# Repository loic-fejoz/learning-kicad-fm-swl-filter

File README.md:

---
title: De rien à un filtre FM pour SWL
author: Loïc Féjoz
date: September, 2022
fontfamily: times
---
De rien à un filtre FM pour SWL
===============================

# Objectifs

> "Dans un voyage ce n'est pas la destination qui compte mais toujours le chemin parcouru, et les détours surtout."  
> — <cite>Philippe Pollet-Villard</cite>

Vous avez acheté une clef SDR ? Moi aussi. Vous avez commencé à faire un peu d'écoute. Peut-être avez-vous fabriqué votre propre antenne aussi ? Viens alors l'idée de passer à la vitesse supérieure et fabriquer vos propres circuits comme un transceiver par exemple, ou un LNA ou...

Mais ces circuits sont déjà d'un niveau supérieur. J'ai donc voulu expérimenter la création d'une carte plus simple depuis sa conception, son analyse, jusqu'à son expérimentation. Or les ondes de station FM se superposent souvent au signal que l'on veut écouter diminuant par la même la dynamique que l'on perçoit. Dés lors le voyage dans la création d'un **filtre passe-haut** peut commencer ...avec ses détours!

NB&nbsp;: vous l'aurez compris, je suis un [n00b](https://fr.wikipedia.org/wiki/Newbie).

Autres projets similaires dans l'esprit :

* [Filtre coupe-bande FM 88 à 108MHz, de la conception à la réalisation](https://www.f4iha.fr/2021/10/16/filtre-coupe-bande-fm-88-a-108mhz-de-la-conception-a-la-realisation/)

# Conception

Bien évidemment un filtre coupe-bande FM serait probablement plus approprié, surtout s'il est bien net. Mais je voulais quelque chose d'encore plus simple. Retrouvons nous donc sur https://rf-tools.com/lc-filter/ pour concevoir ce filtre de Chebyshev d'ordre 5 avec pour fréquence de coupure 120MHz. Les impédances d'entrée et de sortie seront bien entendus de 50Ω comme l'antene et la clef SDR. 

Au final, ce sera donc 3 condensateurs, 2 inductances, et bien sûr 2 connecteurs SMA. Au passage, rf-tools.com peut aussi fournir des valeurs standardisées mais nous n'allons pas utiliser cette fonctionalité qui sera l'occasion d'un détour.

# Schématique KiCad

Il est donc temps maintenant de passer sous KiCad pour éditer la schématique du projet. Cette étape est relativement aisée et il n'y a pas besoin de faire appel à des librairies externes.

Au passage, le connecteur SMA est un connecteur coaxial générique et "SMA" n'est que le label :

Comme on peut le voir dans la boite de dialogue ci-dessus, on peut définir un modèle spice. Or Spice, c'est pour de la simulation. Directement dans KiCad, il est en effet possible d'[inspecter par simulation le circuit](https://www.kicad.org/discover/spice/). Dans notre cas, il faut donc remplacer J2 par une simple résistance :

J1 devrait être remplacée par une source alternative en série avec une résistance de 50Ω. Mais là, rien de vraiment simple dans cette boite de dialogue. Enfin si, on pourrait utiliser un modèle externe. C'est-à-dire créé un fichier `.lib` qui décrirait cette source alternative et la résistance en série. Mais il apparait alors plus simple de rajouter dans le schéma les élements de simulation :

Il y a même une catégorie de composants "pspice". Par contre, il faut tout de même indiquer qu'ils ne font pas partie véritablement de la liste du matériel ainsi que du circuit imprimé.

Enfin, concernant la source de tension, il faudra la configurer en source alternative d'amplitude 1. La fréquence n'aura pas de conséquence vu les analyses que l'on fera.

# Simulation Spice dans KiCad

Il est temps de lancer la simulation via le menu `Inspecter > Simulateur...` ce qui ouvrira la fenêtre dédiée. Le bouton `Paramètres Sim` ouvrira la boîte de dialogue suivante :

Une fois l'analyse désirée indiqué, à savoir analyser la réponse en fréquence sur la place 80MHz-180MHz par exemple, puis avoir lancer la simulation, on peut alors utiliser le bouton `Sonde` pour aller choisir *sur le schéma* le point de sortie du filtre. On voit alors apparaître la réponse de notre filtre :

On retrouve bien la courbe caractéristique d'un filtre passe-haut. Mais nous avions laissé de côté la valeur des composants à réellement utiliser et si vous avez bien observé, les valeurs sont même différentes dans mes différentes captures d'écran. Il est donc temps de comprendre l'impact de ces valeurs. On peut tester l'impact en restant dans KiCad avec le bouton `Ajustage` puis en sélectionnant un composant. Mais J'aimerais une visualisation plus systématique...

# Simulation LTSpice

Il existe plusieurs simulateurs Spice et KiCad permet facilement d'exporter notre schéma dans ce format via le menu `Exporter > Netliste... > Spice`.

[LTSpice](https://www.analog.com/en/design-center/design-tools-and-calculators/ltspice-simulator.html) est un de ces simulateurs qui peut donc analyser ce circuit. Il suffit de rajouter la ligne suivante dans le fichier (avant le `.end`) pour lancer la même analyse:

```spice
.ac LIN 100 88Meg 180Meg
```

Bien évidement, nous retrouvons alors le même résultat que directement dans KiCad. Mais Spice permet bien plus. Nous pouvons notamment définir des variables globales et demander au simulateur de lancer plusieurs simulations. Par exemple, on peut évaluer une liste précise de valeurs comme suit :

```spice
...
L1 Net-_C1-Pad2_ GND {L}
...
.step param L LIST 40nH 41nH 0.0426uH 45nH 48nH
```

Ou bien encore définir une borne haute, et basse, ainsi que l'incrément

```
...
C2 Net-_C1-Pad2_ Net-_C2-Pad2_ {C2}
...
.step param C2 10p 14p 2p
```

Après avoir un peu joué avec les analyses, et sachant que je compte faire l'inductance à la main, je cherche à choisir les valeurs des condensateurs parmi la série E24(±5%).

Cela m'amène à choisir les valeurs de 12pF et 22pF respectivement. Et pour comprendre quelle est la précision attendue dans la réalisation de l'impédance, je simule encore la variation de l'inductance.

NB: une `*` en début de ligne passe celle-ci en commentaire.

Il faudra effectivement viser entre 47nH et 48nH.

# KiCad PCB

Retour dans KiCad pour lancer l'outil d'affectation d'empreinte afin de pouvoir commencer la création du PCB. Comme j'envisage d'utiliser le filtre pour du SWL, je n'ai pas de problème de puissance, et je choisi donc des condensateurs SMD en taille 0805.

Pour les inductances, il faudrait savoir quelle taille pourrait faire une bobines à air faite à la main. L'utilitaire mini Tore Calculateur peut être d'une grande utilité pour cela. Pour simplifier, j'ai cherché un nombre entier de tours et des valeurs réalisables :

Et j'ai pu trouver des empreintes d'inductances déjà existances avec de telles dimensions, ce qui renforce la confiance dans le réalisme espéré.

Nous avons donc maintenant une idée de la taille des composants. Nous savons aussi qu'il nous faudra utiliser un PCB double faces pour avoir un bon plan de masse et utiliser plein de vias. Mais comment choisir la taille des pistes&nbsp;? En fait, cela va dépendre des caractéristiques du support PCB utilisé, en particulier l'épaisseur du substrat et des couches. Heureusement, KiCad possède un outil de calcul. En supposant que l'on désire une impédance d'entrée (resp. de sortie) de 50&ohm; et que l'on désire un PCB de 1,6mm d'épaisseur hors-tout, et d'une couche de cuivre de 1 oz (35&micro;m), nous pouvons synthétiser alors les résultats suivant&nbsp;:

Nous pouvons alors rajouter cette contrainte (0,85mm ou 1,069mm selon le type de PCB) dans les règles de conception comme ceci&nbsp;:

NB&nbsp;: Bien sûr l'impact sera anectodique sur ce circuit en particulier, mais autant prendre de bons réflexes.

A ce stade, nous avons quelques choses comme cela&nbsp;:

Il nous faut maintenant passer à la réalisation...

# Réalisation

## à la mano

C'est parti pour une première réalisation "à la main" du circuit. Comme on peut le voir sur la photo suivante je n'ai pas eu le courage de faire autant de vias que prévu. 😬

Et maintenant place aux mesures ! La pince crocodile bleue sert de mise à la masse du plan de masse en dessous pour ne pas être perturbé par un effet capacitif. Plutôt concluant et correct, non ?

## 1ére commande en ligne

Même principe mais avec un PCB fabriqué par [JLCPCB](https://jlcpcb.com/).
Encore une fois les inductances ont été réalisées à la main autour d'un forêt de ⌀4mm. Mais voyez-vous le problème venir ? Sur cette réalisation, il n'y a pas de séparation de découplage des 2 inductances. Du coup, le filtre ne fonctionne pas du tout comme prévu évidement. L'effet est beaucoup plus notable que ce à quoi je m'attendais.

Deux solutions possibles :

1. on remet une séparation.
2. on place les inductances à 90° pour réduire l'effet.

Pour un premier PCB, c'est à la fois simple mais instructif ! Essayons de faire mieux maintenant.

## 2ème commande en ligne

Outre le problème de couplage des inductances, l'empreinte du connecteur SMA n'était pas le bon car trop espacée. Enfin, il n'y avait rien de prévu pour la fixation de la carte en elle-même.

Donc après de nombreuses recherches, dans l'éditeur de PCB, on peut rajouter des empreintes d'un _mounting hole_ pour le support de la carte. La difficulté réside dans l'étape fastidieuse de changer le mode de _connexion des pads_ en _solide_. A l'inverse, les trous de support de la cloison sont aussi des _Pin_D1.0mm_L10.0mm_LooseFit_ mais avec un mode de _connexion des pads_ de type _frein thermique_ afin de faciliter le soudage.

TODO: commander et mesurer!

## La suite

Une de mes prochaines lectures sera [CEM - Parasites et perturbations des électroniques, Alain Charoy](https://www.dunod.com/sciences-techniques/cem-parasites-et-perturbations-electroniques-tome-1) alors qui sait ce que je vais découvrir... Peut-être un meilleur placement des vias ?

# Remerciements

Merci à tous les radio-amateurs et électroniciens publiants leurs expériences, les youtubeurs pour leurs tutoriels, et les membres du Discord "Radio-Actifs"&nbsp;!

# Bibliographie

* https://alicja.space/blog/designing-lna-with-bandpass-filter
* https://wiki.electrolab.fr/Projets:Perso:2012:Upconverter
* https://rf-tools.com/lc-filter/
* Discord "Radio-Actifs"
* [Youtube KiCad Controlled Impedance Traces (e.g. 50Ω) - Phil's Lab #3](https://www.youtube.com/watch?v=0fteCxn5XXA)
* [Youtube  Top 5 Beginner PCB Design Mistakes (and how to fix them) ](https://www.youtube.com/watch?v=D0X76Kbf8fQ)
* [Youtube  PCB Vias 101 - Phil's Lab #77](https://www.youtube.com/watch?v=WPT96w3eLAM)
* [Youtube  KICAD Prise en mains et premier PCB de A à Z ](https://www.youtube.com/watch?v=dAck3bxzehA)
* [Design a 50 ohm impedance microstrip line for RF signals](https://www.disk91.com/2015/technology/hardware/design-a-50ohm-impedance-net-for-rf-signals/)
* [Calcul et applications des lignes microstrip. - Joël Redoutey - F6CSX](http://f6csx.free.fr/techni/LIGNES%20MICROSTRIP.pdf)
* [PCB pour les n00bs - F6ITU](https://cdn.discordapp.com/attachments/702414448945659945/710137281130004520/PCB_pour_les_n00bs.docx)

# Licence

Ce texte est sous [licence Creative Commons Attribution - Partage dans les Mêmes Conditions 4.0 International (CC BY-SA 4.0)](LICENSE.md)

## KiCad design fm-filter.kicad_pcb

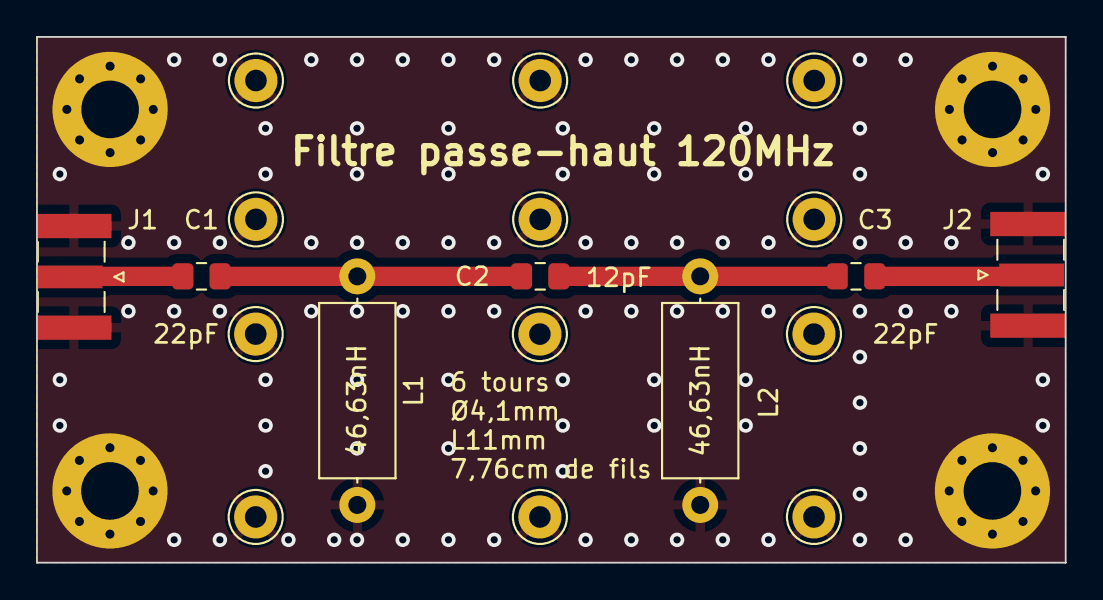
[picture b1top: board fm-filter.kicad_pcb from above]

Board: 2 copper layers, 57.2 x 29.2 mm, 23 parts (0 on the bottom side), 5 nets.

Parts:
C1, C3: 22pF; C_0805_2012Metric_Pad1.18x1.45mm_HandSolder
C2: 12pF; C_0805_2012Metric_Pad1.18x1.45mm_HandSolder
J1, J2: SMA; SMA_Samtec_SMA-J-P-X-ST-EM1_EdgeMount
L1, L2: 46,63nH; L_Axial_L9.5mm_D4.0mm_P12.70mm_Horizontal_Fastron_SMCC
MH1, MH2, MH3, MH4, MH11, MH12, MH13, MH14, MH21, MH22, MH23, MH24: Pin_D1.0mm_L10.0mm_LooseFit
MH_bottom_left: MountingHole_3.2mm_M3_Pad_Via
MH_bottom_right: MountingHole_3.2mm_M3_Pad_Via
MH_top_left: MountingHole_3.2mm_M3_Pad_Via
MH_top_right: MountingHole_3.2mm_M3_Pad_Via

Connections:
GND: J1.2 (Ext), J2.2 (Ext), L1.2, L2.2, MH1.1, MH2.1, MH3.1, MH4.1, MH11.1, MH12.1, MH13.1, MH14.1, MH21.1, MH22.1, MH23.1, MH24.1, MH_bottom_left.1, MH_bottom_right.1, MH_top_left.1, MH_top_right.1
unnamed: C1.2, C2.1, L1.1
unnamed: C2.2, C3.1, L2.1
unnamed: C1.1, J1.1 (In)
unnamed: C3.2, J2.1 (In)

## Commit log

2022-11-27 feat: theoratical study
2023-08-21 feat: separative wall
    Migrate to KiCAD v7.
    Update README.md with initial manual and online order tentative.
    Move to a newer version with mounting holes and pin holes for the wall
    support.
    Test integration with aisler.net
